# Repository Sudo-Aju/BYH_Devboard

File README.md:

<div align="center">

# RP2040 BYH DevBoard

### A compact, beginner-friendly RP2040 development board designed for prototyping, learning, and embedded projects.

<br>

</div>

---

# Overview

The **BYH DevBoard** is a custom development board built around the **Raspberry Pi RP2040** microcontroller. Designed with simplicity and accessibility in mind, it exposes the RP2040's GPIO pins through standard **2.54 mm headers**, making it ideal for breadboarding, prototyping, and embedded development.

The board features **16 MB of SPI Flash**, USB-C connectivity for programming and power, onboard power regulation, and all of the essential support circuitry required by the RP2040.

---

# Features

* Raspberry Pi RP2040 Microcontroller
* Dual-core ARM Cortex-M0+ @ 133 MHz
* 16 MB SPI Flash Storage
* USB Type-C Interface
* 2.54 mm Breakout Headers
* Onboard 3.3 V LDO Regulator
* Compact Surface-Mount Design
* Breadboard Friendly
* Open Hardware Design

---

# Hardware Specifications

| Component         | Specification   |
| ----------------- | --------------- |
| Microcontroller   | RP2040          |
| Flash Memory      | 16 MB SPI Flash |
| USB               | USB Type-C      |
| Operating Voltage | 3.3 V           |
| Crystal           | 12 MHz          |
| GPIO Access       | 2.54 mm Headers |
| PCB               | Custom FR4 PCB  |

---

# PCB Design

### Schematic

### PCB Layout

---

# Components & Ordering

<p align="center">

<br>

</p>

---

# Bill of Materials

## Core Components

| Component            | Qty | Description          |
| -------------------- | --: | -------------------- |
| Custom PCB           |   5 | 1.6 mm FR4, HASL     |
| RP2040 MCU           |   1 | Raspberry Pi RP2040  |
| 16 MB SPI Flash      |   1 | Winbond W25Q16JVZPIQ |
| 3.3 V LDO            |   3 | MCP1700T-3302E       |
| 12 MHz Crystal       |   3 | YSX321SL             |
| USB Type-C Connector |   3 | 16-Pin SMD           |
| 2.54 mm Headers      |   3 | 1×40 SMT             |
| Tactile Switch       |   3 | Boot & Reset         |

---

## Passive Components (0402)

| Component         | Qty |
| ----------------- | --: |
| 100 nF Capacitors |  45 |
| 1 µF Capacitors   |  20 |
| 10 µF Capacitors  |  10 |
| 33 pF Capacitors  |  20 |
| 27 Ω Resistors    |  20 |
| 5.1 kΩ Resistors  |  20 |
| 1 kΩ Resistors    |  20 |
| 10 kΩ Resistors   |  20 |

---

# Estimated Cost

| Category                 |          Cost |
| ------------------------ | ------------: |
| Core Components          | **₹2,290.00** |
| Passive Components       |   **₹224.85** |
| **Total Estimated Cost** | **₹2,514.85** |

---

# Pinout

The BYH DevBoard exposes nearly every RP2040 GPIO pin through standard **2.54 mm headers**, making it compatible with breadboards, jumper wires, sensors, displays, and common development modules.

---

# Why I Built It

Commercial RP2040 development boards are excellent, but I wanted to understand what goes into designing one from scratch.

This project gave me hands-on experience with:

* RP2040 reference design
* High-speed USB routing
* Power supply design
* PCB layout best practices
* Component sourcing
* Manufacturing preparation
* Hardware documentation

---

# Future Improvements

* USB ESD Protection
* Power LED
* User Programmable LED
* SWD Debug Header
* Castellated Edge Version
* Battery Support

---

<div align="center">

### Designed from scratch to learn hardware by building it.

</div>

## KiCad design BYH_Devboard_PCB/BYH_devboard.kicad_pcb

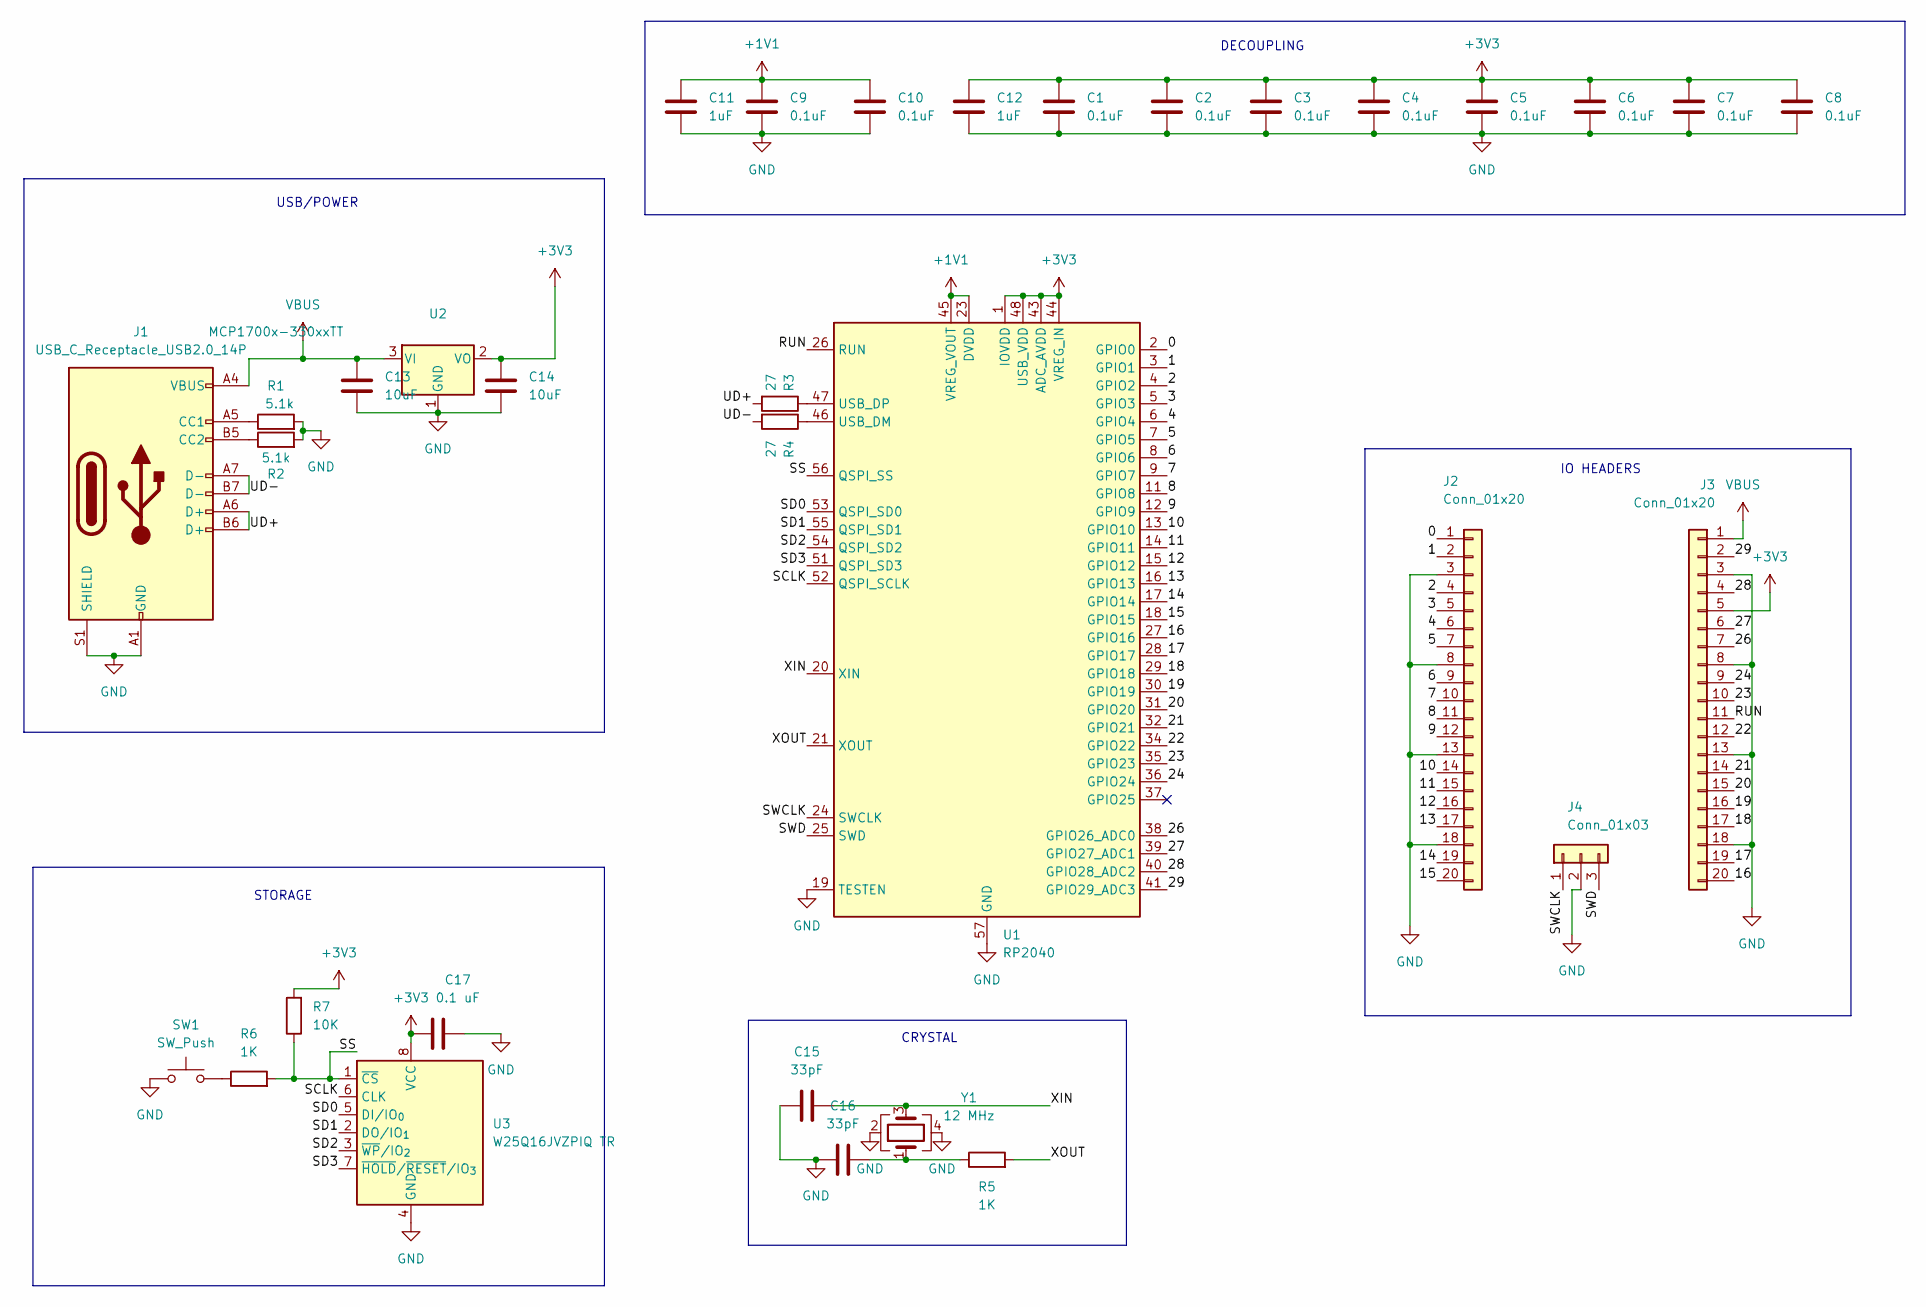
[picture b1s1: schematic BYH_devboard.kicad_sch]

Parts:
C1, C2, C3, C4, C5, C6, C7, C8, C9, C10: 0.1uF; C_0402_1005Metric
C11, C12: 1uF; C_0402_1005Metric
C13, C14: 10uF; C_0402_1005Metric
C15, C16: 33pF; C_0402_1005Metric
C17: 0.1 uF; C_0402_1005Metric
J1: USB_C_Receptacle_USB2.0_14P; USB_C_Receptacle_HRO_TYPE-C-31-M-12
J2, J3: Conn_01x20; PinHeader_1x20_P2.54mm_Vertical
J4: Conn_01x03; PinHeader_1x03_P2.54mm_Vertical
R1, R2: 5.1k; R_0402_1005Metric
R3, R4: 27; R_0402_1005Metric
R5, R6: 1K; R_0402_1005Metric
R7: 10K; R_0402_1005Metric
SW1: SW_Push; SW_Push_SPST_NO_Alps_SKRK
U1: RP2040; QFN-56-1EP_7x7mm_P0.4mm_EP3.2x3.2mm
U2: MCP1700x-330xxTT; SOT-23
U3: W25Q16JVZPIQ TR; Winbond_USON-8-1EP_3x2mm_P0.5mm_EP0.2x1.6mm
Y1: 12 MHz; Crystal_SMD_3225-4Pin_3.2x2.5mm

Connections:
+1V1: C9.1, C10.1, C11.1, U1.23 (DVDD), U1.45 (VREG_VOUT), U1.50 (DVDD)
+3V3: C1.1, C2.1, C3.1, C4.1, C5.1, C6.1, C7.1, C8.1, C12.1, C14.1, C17.1, J3.5, R7.2, U1.1 (IOVDD), U1.10 (IOVDD), U1.22 (IOVDD), U1.33 (IOVDD), U1.42 (IOVDD), U1.43 (ADC_AVDD), U1.44 (VREG_IN), U1.48 (USB_VDD), U1.49 (IOVDD), U2.2 (VO), U3.8 (VCC)
/0: J2.1, U1.2 (GPIO0)
/1: J2.2, U1.3 (GPIO1)
/2: J2.4, U1.4 (GPIO2)
/3: J2.5, U1.5 (GPIO3)
/4: J2.6, U1.6 (GPIO4)
/5: J2.7, U1.7 (GPIO5)
/6: J2.9, U1.8 (GPIO6)
/7: J2.10, U1.9 (GPIO7)
/8: J2.11, U1.11 (GPIO8)
/9: J2.12, U1.12 (GPIO9)
/10: J2.14, U1.13 (GPIO10)
/11: J2.15, U1.14 (GPIO11)
/12: J2.16, U1.15 (GPIO12)
/13: J2.17, U1.16 (GPIO13)
/14: J2.19, U1.17 (GPIO14)
/15: J2.20, U1.18 (GPIO15)
/16: J3.20, U1.27 (GPIO16)
/17: J3.19, U1.28 (GPIO17)
/18: J3.17, U1.29 (GPIO18)
/19: J3.16, U1.30 (GPIO19)
/20: J3.15, U1.31 (GPIO20)
/21: J3.14, U1.32 (GPIO21)
/22: J3.12, U1.34 (GPIO22)
/23: J3.10, U1.35 (GPIO23)
/24: J3.9, U1.36 (GPIO24)
/26: J3.7, U1.38 (GPIO26_ADC0)
/27: J3.6, U1.39 (GPIO27_ADC1)
/28: J3.4, U1.40 (GPIO28_ADC2)
/29: J3.2, U1.41 (GPIO29_ADC3)
/RUN: J3.11, U1.26 (RUN)
/SCLK: U1.52 (QSPI_SCLK), U3.6 (CLK)
/SD0: U1.53 (QSPI_SD0), U3.5 (DI/IO_{0})
/SD1: U1.55 (QSPI_SD1), U3.2 (DO/IO_{1})
/SD2: U1.54 (QSPI_SD2), U3.3 (~WP/IO_{2})
/SD3: U1.51 (QSPI_SD3), U3.7 (~HOLD/~RESET/IO_{3})
/SS: R6.2, R7.1, U1.56 (QSPI_SS), U3.1 (~CS)
/SWCLK: J4.1, U1.24 (SWCLK)
/SWD: J4.3, U1.25 (SWD)
/UD+: J1.A6 (D+), J1.B6 (D+), R3.2
/UD-: J1.A7 (D-), J1.B7 (D-), R4.2
/XIN: C15.2, U1.20 (XIN), Y1.3
/XOUT: R5.2, U1.21 (XOUT)
GND: C1.2, C2.2, C3.2, C4.2, C5.2, C6.2, C7.2, C8.2, C9.2, C10.2, C11.2, C12.2, C13.2, C14.2, C15.1, C16.2, C17.2, J1.A1 (GND), J1.A12 (GND), J1.B1 (GND), J1.B12 (GND), J1.S1 (SHIELD), J2.3, J2.8, J2.13, J2.18, J3.3, J3.8, J3.13, J3.18, J4.2, R1.2, R2.2, SW1.1, U1.19 (TESTEN), U1.57 (GND), U2.1 (GND), U3.4 (GND), Y1.2, Y1.4
unnamed: C16.1, R5.1, Y1.1
unnamed: J1.A5 (CC1), R1.1
unnamed: J1.B5 (CC2), R2.1
unnamed: R6.1, SW1.2
unnamed: R4.1, U1.46 (USB_DM)
unnamed: R3.1, U1.47 (USB_DP)
VBUS: C13.1, J1.A4 (VBUS), J1.A9 (VBUS), J1.B4 (VBUS), J1.B9 (VBUS), J3.1, U2.3 (VI)

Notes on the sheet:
CRYSTAL
DECOUPLING
IO HEADERS
USB/POWER
STORAGE

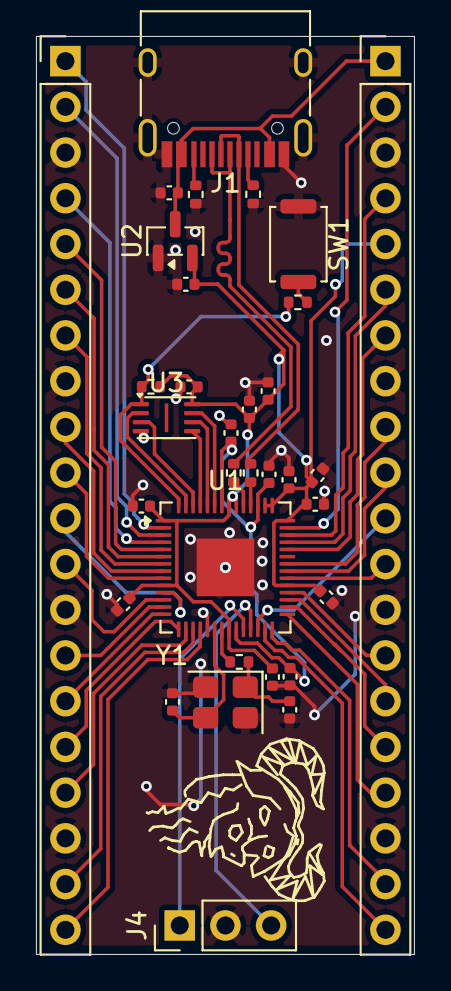
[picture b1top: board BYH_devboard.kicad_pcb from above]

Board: 2 copper layers, 21.0 x 51.0 mm, 33 parts (0 on the bottom side), 52 nets.

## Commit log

2026-01-31 Added PCB design and schematics with gerber files
2026-01-31 redid the Readme with BOM and other things
2026-01-31 Add additional screenshots to README
2026-01-31 Add Devboard render image to README
    Added an image of the Devboard render to the README.
